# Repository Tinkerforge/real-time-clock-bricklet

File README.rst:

Real-Time Clock Bricklet
========================

This repository contains the firmware source code and the hardware design
files. The documentation generator configs can be found at
https://github.com/Tinkerforge/generators

Repository Content
------------------

software/:
 * examples/: Examples for all supported languages
 * build/: Compiled files
 * src/: Source code of firmware
 * Makefile: Makefile to build project

hardware/:
 * Contains KiCad project files and additionally schematics as PDF

datasheets/:
 * Contains datasheets for sensors and complex ICs that are used

Hardware
--------

The hardware is designed with the open source EDA Suite KiCad
(http://www.kicad.org). Before you are able to open the files,
you have to install the Tinkerforge kicad-libraries
(https://github.com/Tinkerforge/kicad-libraries). You can either clone
them directly in hardware/ or clone them in a separate folder and
symlink them into hardware/
(ln -s kicad_path/kicad-libraries project_path/hardware). After that you
can open the .pro file in hardware/ with KiCad and from there view and
modify the schematics and the PCB layout.

Software
--------

If you want to do your own Brick/Bricklet firmware development we highly
recommend that you use our build environment setup script and read the
tutorial (https://www.tinkerforge.com/en/doc/Tutorials/Tutorial_Build_Environment/Tutorial.html).

To compile the C code we recommend you to install the newest GNU Arm Embedded
Toolchain (https://launchpad.net/gcc-arm-embedded/+download).
You also need to install bricklib (https://github.com/Tinkerforge/bricklib)
and brickletlib (https://github.com/Tinkerforge/brickletlib).

You can either clone it directly in software/src/ or clone it in a
separate folder and symlink it into software/src/
(ln -s bricklib_path/bricklib project_path/software/src/ and
ln -s brickletlib_path/brickletlib project_path/software/src/).
Finally make sure to have CMake installed
(http://www.cmake.org/cmake/resources/software.html).

After that you can build the firmware by invoking make in software/.
The firmware (.bin) can then be found in software/build/ and uploaded
with brickv (click button "Flashing" on start screen).

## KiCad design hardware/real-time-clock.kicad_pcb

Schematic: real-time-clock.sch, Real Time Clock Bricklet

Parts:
BT1: BATTERY; BATTERY_HOLDER_2998
C1, C2, C3: 100nF; C0603E
P1: CON-SENSOR
RP1: 2k2; 4X0603
U1: M24C64; SOIC8
U2: PCF85263AT; SO-8
U3, U4, U5, U6: DRILL; DRILL_NP
X1: 32.768kHz; AB26TRQ

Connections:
3V3: C1.1, C2.1, P1.3 (3.3V), RP1.5 (R4), RP1.6 (R3), RP1.7 (R2), RP1.8 (R1), U1.8 (VCC), U2.8 (VDD)
GND: BT1.2, C1.2, C2.2, C3.2, P1.2 (GND), P1.EP, U1.1 (A01), U1.2 (A02), U1.4 (VSS), U2.4 (VSS), X1.3
unnamed: BT1.1, C3.1, U2.3 (VBAT)
unnamed: P1.6 (ADDR), U1.3 (A03)
unnamed: P1.7 (IO_1/AD), RP1.3, U2.5 (SDA)
unnamed: P1.8 (IO_2/DA), RP1.2, U2.6 (SCL)
unnamed: P1.9 (IO_3/PWM), RP1.1, U2.7 (nINTA)
unnamed: U2.1 (OSCI), X1.2
unnamed: U2.2 (OSCO), X1.1
SCL: P1.4 (SCL), U1.6 (SCL)
SDA: P1.5 (SDA), U1.5 (SDA)

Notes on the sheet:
Copyright Tinkerforge GmbH 2015. This documentation describes Open Hardware and is licensed under the CERN OHL v. 1.1. You may redistribute and modify this documentation under the terms of the CERN OHL v.1.1. (http://ohwr.org/cernohl). This documentation is distributed WITHOUT ANY EXPRESS OR IMPLIE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
CL = 6,7,12.5pF
Digikey 36-2998-ND
AB26TRQ-32.768kHz-T
364, LR621, AG1 or 321, SR616

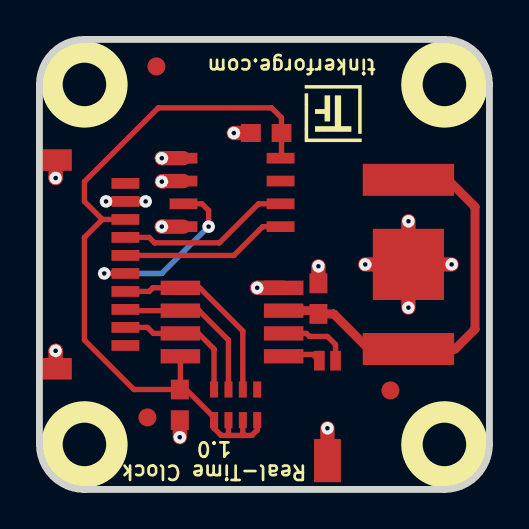
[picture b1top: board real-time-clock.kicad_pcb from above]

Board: 2 copper layers, 25.0 x 25.0 mm, 18 parts (0 on the bottom side), 11 nets.

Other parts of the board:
Fiducial_Mark: VAL**; Fiducial_Mark
Fiducial_Mark#2, Fiducial_Mark#3: VAL**; Fiducial_Mark
VAL: WEEE_7mm_back
VAL#2: CE_5mm

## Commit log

2015-11-11 initial commit, hardware files copied of can bricklet, schematic partially adapted
2015-11-17 fully routed
2015-11-17 fix description
2015-12-30 Add PCF85263A datasheet
2016-01-21 Add .gitignore
2016-01-21 Mostly feature complete
2016-01-22 Reorganize code to make it fit into 4k
2016-01-22 Enable 100th second mode
2016-01-22 Add get/set_user_data API
2016-01-22 Reorder calibration bytes to start with the magic number
2016-01-26 Write user-data to correct register
2016-01-26 Simplify API and focus on the time keeping aspect
2016-01-26 Add crystal datasheet
2016-01-26 Disable unnecessary clock output
2016-01-28 Remove fast offset correction mode
    This mdoe is not usefull as the user cannot measure the offset fast
    enough to make use of the fast mode for temperature compensation.
2016-01-28 Rename get_timestamp result to timestamp
2016-01-28 Add examples
2016-02-01 c: Fix int64_t printf format warning
2016-02-01 change rtc battery footprint
2016-02-01 add fiducials
2016-02-05 Remove unused variables
2016-02-09 Add WIP marker
2016-02-10 schematic file
2016-02-10 Remove WIP marker
2016-02-10 Simplify I2C code
2016-02-10 Add changelog date and commit after the fact
2016-03-30 Restore calibration correctly after reset
2016-03-30 Add date/time and timestamp callbacks
2016-03-31 Add set/get_alarm function and alarm callback
2016-05-13 Add configurable alarm function
    Need to merge date/time and timestamp callback to make room for it.
2016-05-18 c: Add missing device destroy call
2016-05-25 Disallow interval of 0 seconds
2016-06-29 Add callback examples
2016-06-29 Remove unused function
2016-07-01 Make the change UID comment more explicit
2016-08-19 Fix typo
2017-04-13 csharp: Adapt example
2017-06-01 c: Ensure PRId64 is defined
2017-06-02 octave: Use javaObject instead of deprecated java_new
2017-11-20 c: Avoid gcc warning
2017-11-30 Update examples from generator
2017-12-07 mathematica: Also generate .nb files
2018-01-22 Add 3d information (tbc)
2018-01-26 c: Fine-tune printf format
2018-01-30 Add 3d information (final)
2018-01-30 Add 3d model (*.step & *.FCStd)
2018-02-02 Update examples
2018-02-19 javascript: Close div tag correctly
2018-02-20 Cleanup KiCad libraries config
    Ensure LibDir=kicad-libraries and LibName1=tinkerforge.
    Remove special library.
2018-05-11 Rename files
2018-05-24 perl: Use strict in examples
2018-05-28 mathematica: Reorder some lines for clearity
2018-07-11 Add Makefile with docker support
2018-07-11 Remove obsolete generate_makefile scripts
2018-07-11 Update directory structure and build instructions
2018-11-06 Add rust examples
2018-11-07 rust: Accept host names for ip connection, fix naming inconsistencies
2018-11-07 rust: Rename callback receivers.
2018-12-14 Add go examples.
2018-12-18 go: Change import path.
2018-12-18 go: Change import path again.
2018-12-20 Fix constant handling in examples.
2018-12-20 rust: Reformat examples.
2019-01-24 mqtt: Add examples.
2019-01-24 mqtt: Fix example header.
2019-01-24 mqtt: Remove executable bit in example permissions.
2019-01-24 go: Minor example fixes.
2019-01-24 mqtt: Minor example fixes.
2019-03-28 mqtt: Fix whitespace.
2019-08-22 c: Adapt to bindings changes
2020-01-13 examples: Use python3 input instead of python2 raw_input.
2020-01-13 examples: mqtt: Remove trailing whitespace.
2021-10-25 Update KiCad link
    https://www.kicad.org/blog/2021/10/Avoid-links-to-former-kicad-domain/
2022-05-10 go: Fix format string
2022-07-06 Add license files.

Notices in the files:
hardware/real-time-clock.kicad_pcb:
Licensed under CERN OHL v.1.1
Copyright (©) 2015, B.Nordmeyer
